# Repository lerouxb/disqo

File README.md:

# Disqo

A wearable synthesizer — a smartwatch with three buttons, a high-resolution magnetic scroll wheel and a circular LCD display, designed for building a synth you can run on your wrist.

## Hardware

Disqo is built around a custom PCB designed in KiCad.

| Component | Description |
|---|---|
| **ESP32-PICO-MINI-02** | Espressif SiP with 8 MB flash and 2 MB PSRAM |
| **GC9A01 round LCD** | 240×240 pixel 1.28" circular TFT display over SPI at 80 MHz |
| **AS5600** | 12-bit magnetic rotary encoder over I2C — acts as a high-resolution scroll wheel (like a watch crown) |
| **3 buttons** | Physical inputs for navigation, selection and sleep/wake |
| **Piezo buzzer** | PWM-driven audio output (beep/boop, future synth capabilities) |
| **MCP73831-2** | Single-cell Li-Po battery charger via USB |
| **32.768 kHz crystal** | External RTC clock source for accurate timekeeping |
| **Battery ADC** | Monitors battery voltage |

The PCB files, schematic, BOM and 3D models live in the `pcb/` directory. An interactive HTML BOM is available at `pcb/bom/ibom.html`.

## Firmware

The firmware runs on **MicroPython** with a patched [gc9a01_mpy](https://github.com/russhughes/gc9a01_mpy) C module compiled in for fast display drawing.

### Structure

```
firmware/
├── main.py              # Entry point — launches the watchface
├── boot.py              # MicroPython boot stub
├── apps/                # Applications (clock, main menu)
├── gui/                 # UI framework (menus, themes, text layout)
├── system/              # Hardware abstraction layer (HAL)
├── utils/               # Encoder math, datetime formatting, font helpers
├── fonts/               # Bitmap and TTF font definitions
├── scripts/             # Build, deploy and helper scripts
├── patches/             # Patches for gc9a01_mpy and MicroPython ESP32 port
└── typings/             # MicroPython type stubs for IDE support
```

### Watchface

The current primary watchface features:

- DSEG7-style digital clock with "ghost" segments
- Greeting text that changes by time of day (Good morning / afternoon / evening)
- Battery icon with voltage display
- Date with day-of-week
- Double-buffered rendering with a textured background

### Controls

- **Rotary encoder (scroll wheel):** Scrolls through menus and adjusts values
- **Button 1 (B1):** Wake from deep sleep; back/cancel in menus
- **Button 3 (B3):** Open main menu; select in menus
- **B1 + B3 combo:** Enter deep sleep

### Apps

- **Clock** — Date, time, battery status, encoder angle
- **Main Menu** — Scrollable menu with items: date/time, alarm, theme, brightness, metronome, drone (sub-apps are still planned)

## Building & Deploying

### Prerequisites

- MicroPython source
- ESP-IDF toolchain
- `esptool` and `mpremote`

### Compile MicroPython

The build script compiles MicroPython for the `GENERIC_SPIRAM` board with the patched `gc9a01_mpy` module:

```bash
cd firmware/scripts
./compile-micropython.sh
```

Patches are applied before building:

- **gc9a01_mpy.patch** — Faster display init, adds `draw_len` for text measurement
- **micropython-ports-esp32.patch** — Configures 80 MHz flash/SPIRAM, external RTC crystal, faster deep sleep wake

### Deploy code to device

```bash
cd firmware/scripts
./copy-code.sh
```

This uses `mpremote` to copy the Python source files to the device and syncs the RTC to the host clock.

### Set time

```bash
cd firmware/scripts
./set-time.sh
```

## Future Plans

- **Audio synthesis:** Wrap `pwm_audio` for better piezo output, classic Bluetooth audio, digital audio synthesis libraries
- **Sub-apps:** Date/time setting, alarm, theme selector, brightness control, metronome, drone
- Smarter input polling and debouncing
- Theme persistence in non-volatile memory

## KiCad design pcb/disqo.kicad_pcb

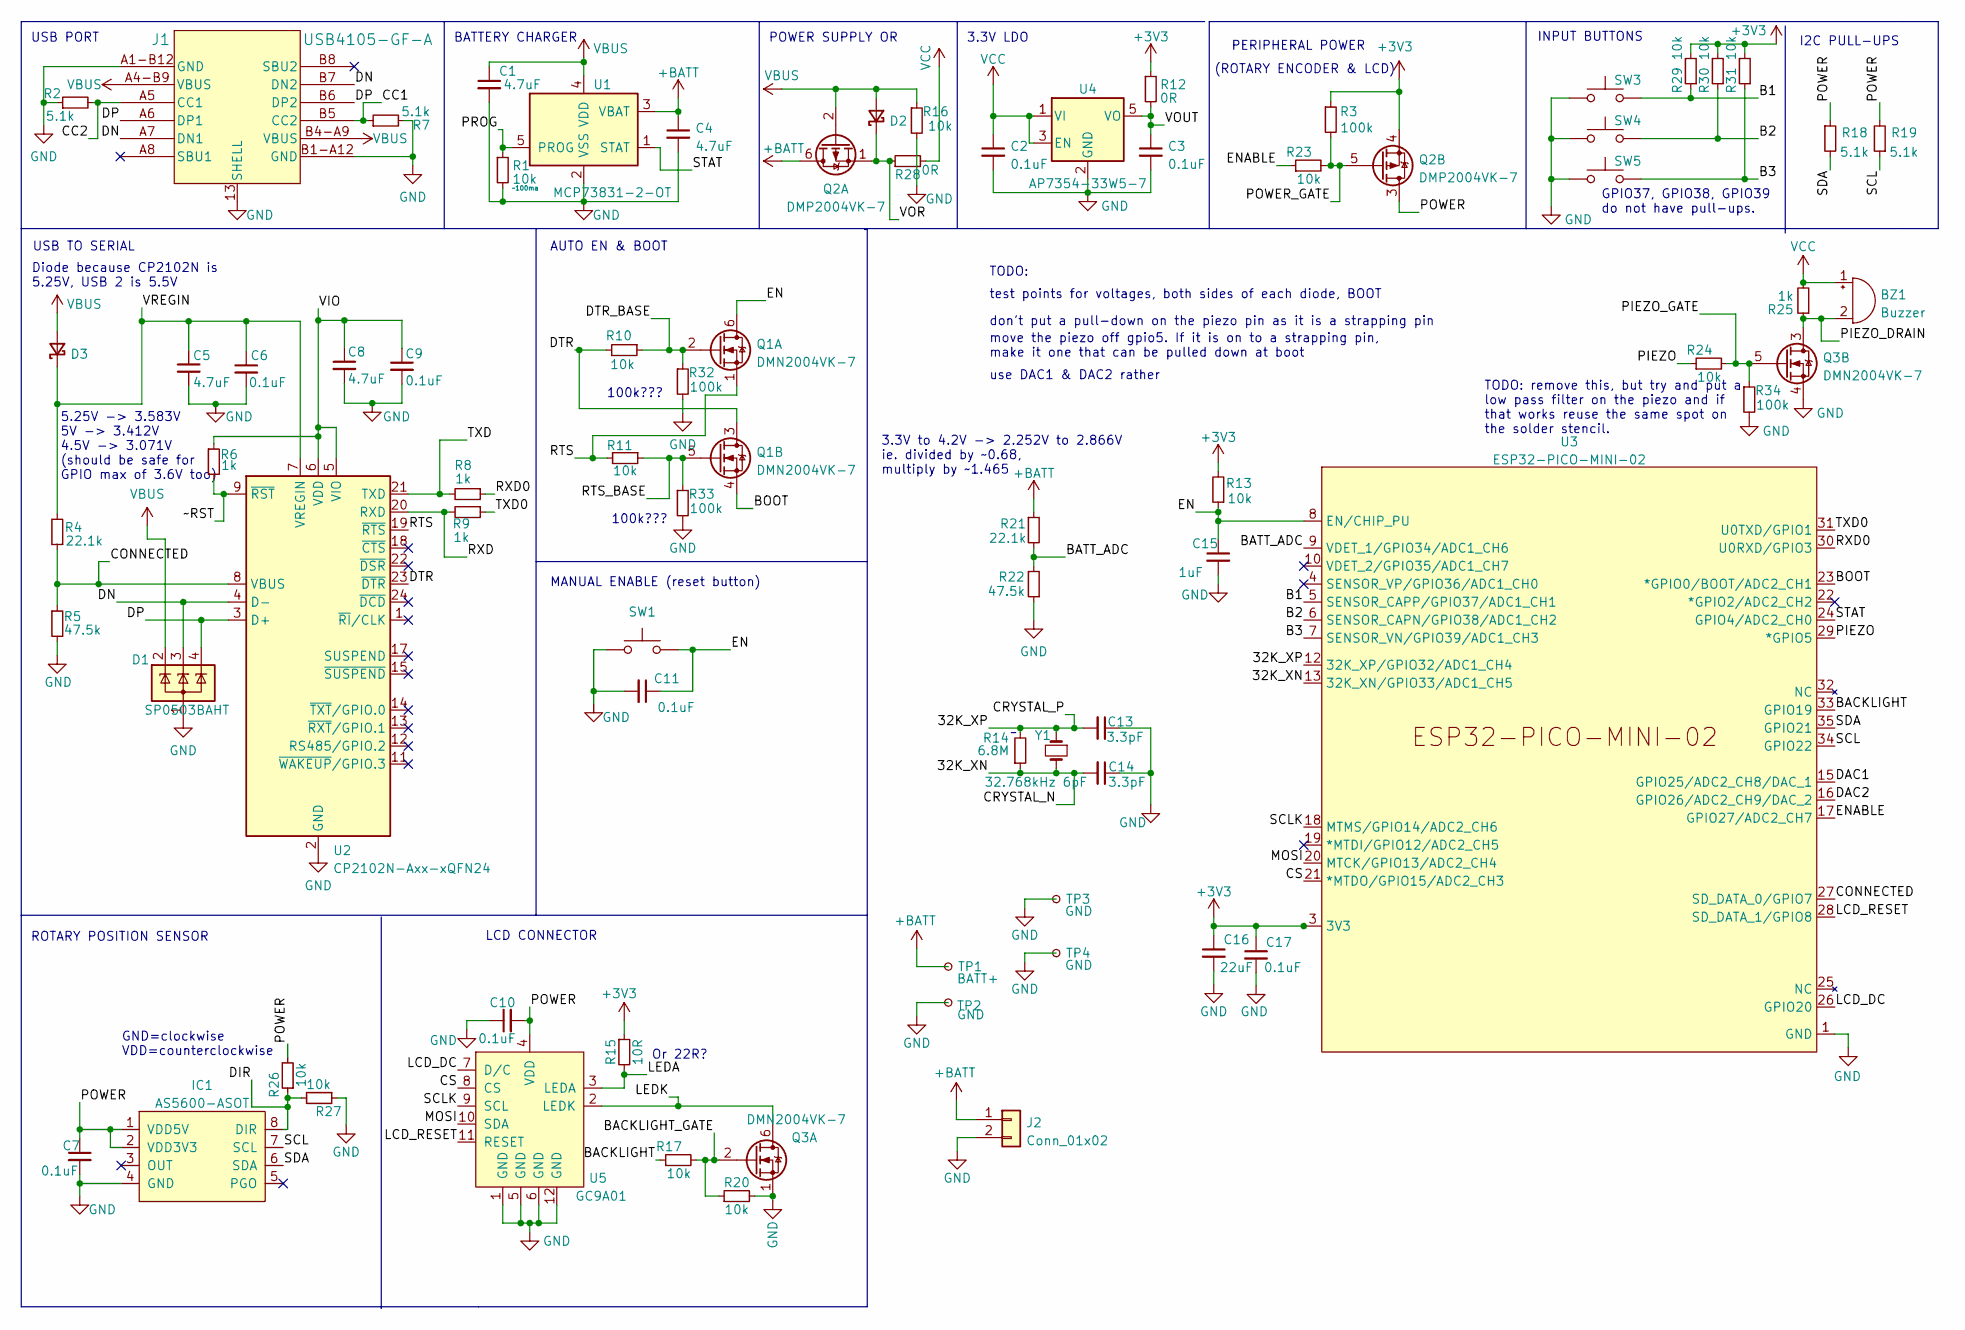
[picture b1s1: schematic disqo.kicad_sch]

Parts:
BZ1: Buzzer; SPKR_PKMCS0909E4000-R1
C1, C4, C5, C8: 4.7uF; C_0805_2012Metric
C2, C3, C6, C7, C9, C10, C11, C17: 0.1uF; C_0402_1005Metric
C13, C14: 3.3pF; C_0603_1608Metric
C15: 1uF; C_0603_1608Metric
C16: 22uF; C_0805_2012Metric
D1: SP0503BAHT; SOT-143
D2, D3: D_Schottky_Small; D_SOD-323
IC1: AS5600-ASOT; SOIC-8_3.9x4.9mm_P1.27mm; MOUSER_PART_NUMBER 985-AS5600-ASOT
J1: USB4105-GF-A
J2: Conn_01x02; JST_ACH_BM02B-ACHSS-GAN-ETF_1x02-1MP_P1.20mm_Vertical
Q1, Q3: DMN2004VK-7; SOT-563
Q2: DMP2004VK-7; SOT-563
R1, R10, R11, R13, R16, R17, R20, R23, R24, R26, R27, R29, R30, R31: 10k; R_0402_1005Metric
R2, R7, R18, R19: 5.1k; R_0402_1005Metric
R3, R32, R33, R34: 100k; R_0402_1005Metric
R4, R21: 22.1k; R_0402_1005Metric
R5, R22: 47.5k; R_0402_1005Metric
R6, R8, R9, R25: 1k; R_0402_1005Metric
R12, R28: 0R; R_0805_2012Metric
R14: 6.8M; R_0603_1608Metric
R15: 10R; R_0402_1005Metric
SW1: top-switch; KXT 311 LHS
SW3, SW4, SW5: side-switch; EVP-AKE31A
TP1: BATT+; TestPoint_THTPad_D1.5mm_Drill0.7mm
TP2: GND; TestPoint_THTPad_D1.5mm_Drill0.7mm
TP3, TP4: GND; tab
U1: MCP73831-2-OT; SOT-23-5
U2: CP2102N-Axx-xQFN24; QFN-24-1EP_4x4mm_P0.5mm_EP2.6x2.6mm
U3: ESP32-PICO-MINI-02; ESP32-PICO-MINI-02_Hand-Soldering
U4: AP7354-33W5-7; SOT-25
U5: GC9A01; GC9A01_IPS_display_under
Y1: 32.768kHz 6pF; Crystal_SMD_3215-2Pin_3.2x1.5mm

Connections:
+3V3: C16.1, C17.1, Q2.4 (S), R3.1, R12.1, R13.2, R15.1, R29.2, R30.2, R31.2, U3.3 (3V3)
+BATT: C4.1, J2.1, Q2.6 (D), R21.1, TP1.1, U1.3 (VBAT)
/32K_XN: C14.2, R14.1, U3.13 (32K_XN/GPIO33/ADC1_CH5), Y1.2
/32K_XP: C13.2, R14.2, U3.12 (32K_XP/GPIO32/ADC1_CH4), Y1.1
/B1: R29.1, SW3.1, U3.5 (SENSOR_CAPP/GPIO37/ADC1_CH1)
/B2: R30.1, SW4.1, U3.6 (SENSOR_CAPN/GPIO38/ADC1_CH2)
/B3: R31.1, SW5.2, U3.7 (SENSOR_VN/GPIO39/ADC1_CH3)
/BACKLIGHT: R17.1, U3.33 (GPIO19)
/BACKLIGHT_GATE: Q3.2 (G), R17.2, R20.1
/BATT_ADC: R21.2, R22.2, U3.9 (VDET_1/GPIO34/ADC1_CH6)
/BOOT: Q1.4 (S), U3.23 (*GPIO0/BOOT/ADC2_CH1)
/CC1: J1.B5 (CC2), R7.1
/CC2: J1.A5 (CC1), R2.2
/CONNECTED: R4.1, R5.1, U2.8 (VBUS), U3.27 (SD_DATA_0/GPIO7)
/CS: U3.21 (*MTDO/GPIO15/ADC2_CH3), U5.8 (CS)
/DAC1: U3.15 (GPIO25/ADC2_CH8/DAC_1)
/DAC2: U3.16 (GPIO26/ADC2_CH9/DAC_2)
/DIR: IC1.8 (DIR), R26.1, R27.2
/DN: D1.3 (K), J1.A7 (DN1), J1.B7 (DN2), U2.4 (D-)
/DP: D1.4 (K), J1.A6 (DP1), J1.B6 (DP2), U2.3 (D+)
/DTR: Q1.3 (D), R10.2, U2.23 (~DTR)
/DTR_BASE: Q1.2 (G), R10.1, R32.1
/EN: C11.1, C15.1, Q1.6 (D), R13.1, SW1.2, U3.8 (EN/CHIP_PU)
/ENABLE: R23.1, U3.17 (GPIO27/ADC2_CH7)
/LCD_DC: U3.26 (GPIO20), U5.7 (D/C)
/LCD_RESET: U3.28 (SD_DATA_1/GPIO8), U5.11 (RESET)
/LEDA: R15.2, U5.3 (LEDA)
/LEDK: Q3.6 (D), U5.2 (LEDK)
/MOSI: U3.20 (MTCK/GPIO13/ADC2_CH4), U5.10 (SDA)
/PIEZO: R24.1, U3.29 (*GPIO5)
/PIEZO_DRAIN: BZ1.2 (+), Q3.3 (D), R25.1
/PIEZO_GATE: Q3.5 (G), R24.2, R34.1
/POWER: C7.1, C10.2, IC1.1 (VDD5V), IC1.2 (VDD3V3), Q2.3 (D), R18.1, R19.2, R26.2, U5.4 (VDD)
/POWER_GATE: Q2.5 (G), R3.2, R23.2
/PROG: R1.1, U1.5 (PROG)
/RTS: Q1.1 (S), R11.2, U2.19 (~RTS)
/RTS_BASE: Q1.5 (G), R11.1, R33.1
/RXD: R9.2, U2.20 (RXD)
/RXD0: R8.1, U3.30 (U0RXD/GPIO3)
/SCL: IC1.7 (SCL), R19.1, U3.34 (GPIO22)
/SCLK: U3.18 (MTMS/GPIO14/ADC2_CH6), U5.9 (SCL)
/SDA: IC1.6 (SDA), R18.2, U3.35 (GPIO21)
/STAT: U1.1 (STAT), U3.24 (GPIO4/ADC2_CH0)
/TXD: R8.2, U2.21 (TXD)
/TXD0: R9.1, U3.31 (U0TXD/GPIO1)
/VIO: C8.1, C9.1, R6.1, U2.5 (VIO), U2.6 (VDD)
/VOR: D2.1 (K), Q2.1 (S), R28.1
/VOUT: C3.1, R12.2, U4.5 (VO)
/VREGIN: C5.1, C6.1, D3.1 (K), R4.2, U2.7 (VREGIN)
/~RST: R6.2, U2.9 (~RST)
GND: C1.2, C2.2, C3.2, C4.2, C5.2, C6.2, C7.2, C8.2, C9.2, C10.1, C11.2, C13.1, C14.1, C15.2, C16.2, C17.2, D1.1 (A), IC1.4 (GND), J1.13 (SHELL), J1.A1-B12 (GND), J1.B1-A12 (GND), J2.2, Q3.1 (S), Q3.4 (S), R1.2, R2.1, R5.2, R7.2, R16.2, R20.2, R22.1, R27.1, R32.2, R33.2, R34.2, SW1.1, SW3.2, SW4.2, SW5.1, TP2.1, TP3.1, TP4.1, U1.2 (VSS), U2.2 (GND), U2.25 (GND), U3.1 (GND), U3.2 (GND), U3.11 (GND), U3.14 (GND), U3.36 (GND), U4.2 (GND), U5.1 (GND), U5.5 (GND), U5.6 (GND), U5.12 (GND)
VBUS: C1.1, D1.2 (K), D2.2 (A), D3.2 (A), J1.A4-B9 (VBUS), J1.B4-A9 (VBUS), Q2.2 (G), R16.1, U1.4 (VDD)
VCC: BZ1.1 (-), C2.1, R25.2, R28.2, U4.1 (VI), U4.3 (EN)

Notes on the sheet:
POWER SUPPLY OR
use DAC1 & DAC2 rather
PERIPHERAL POWER
GPIO37, GPIO38, GPIO39 do not have pull-ups.
INPUT BUTTONS
3.3V LDO
(ROTARY ENCODER & LCD)
move the piezo off gpio5. If it is on to a strapping pin, make it one that can be pulled down at boot
5.25V -> 3.583V 5V -> 3.412V 4.5V -> 3.071V (should be safe for GPIO max of 3.6V too)
I2C PULL-UPS
100k???
USB TO SERIAL
TODO: remove this, but try and put a low pass filter on the piezo and if that works reuse the same spot on the solder stencil.
LCD CONNECTOR
AUTO EN & BOOT
Or 22R?
BATTERY CHARGER
don't put a pull-down on the piezo pin as it is a strapping pin
USB PORT
GND=clockwise VDD=counterclockwise
MANUAL ENABLE (reset button)
3.3V to 4.2V -> 2.252V to 2.866V ie. divided by ~0.68, multiply by ~1.465
test points for voltages, both sides of each diode, BOOT
Diode because CP2102N is 5.25V, USB 2 is 5.5V
ROTARY POSITION SENSOR
TODO:

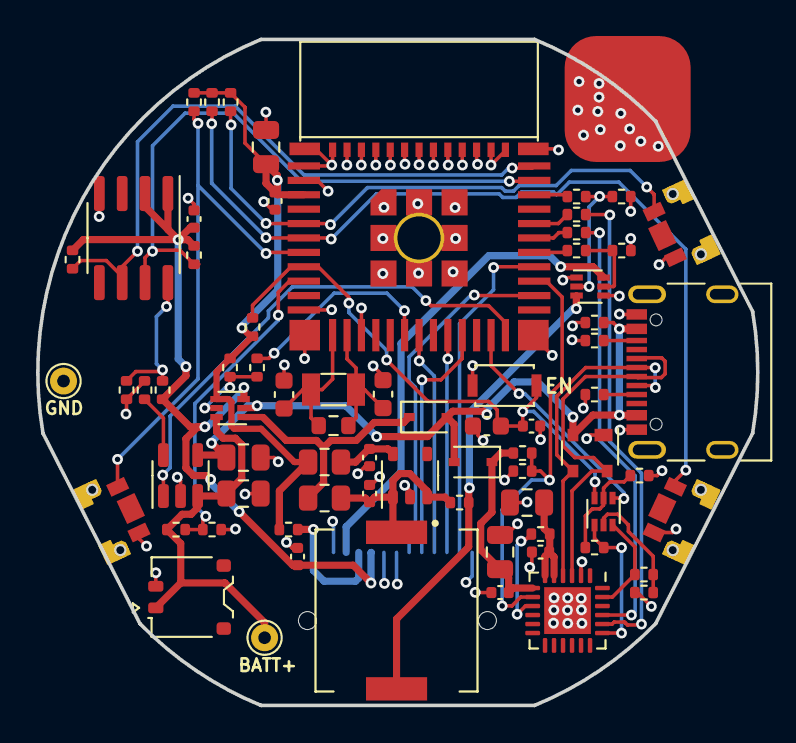
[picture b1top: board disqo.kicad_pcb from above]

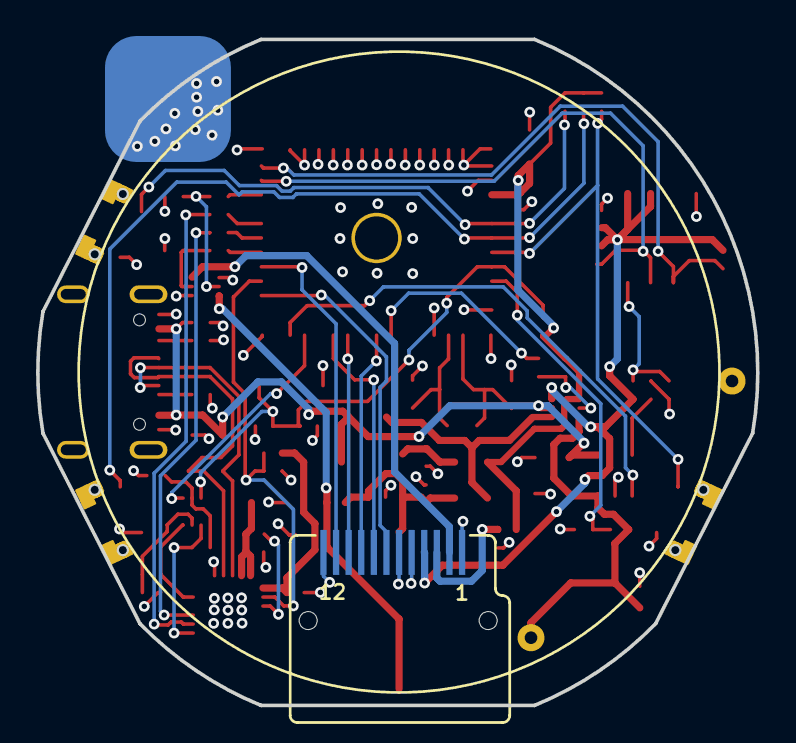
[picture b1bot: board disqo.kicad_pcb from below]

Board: 4 copper layers, 40.0 x 37.0 mm, 74 parts (2 on the bottom side), 51 nets.

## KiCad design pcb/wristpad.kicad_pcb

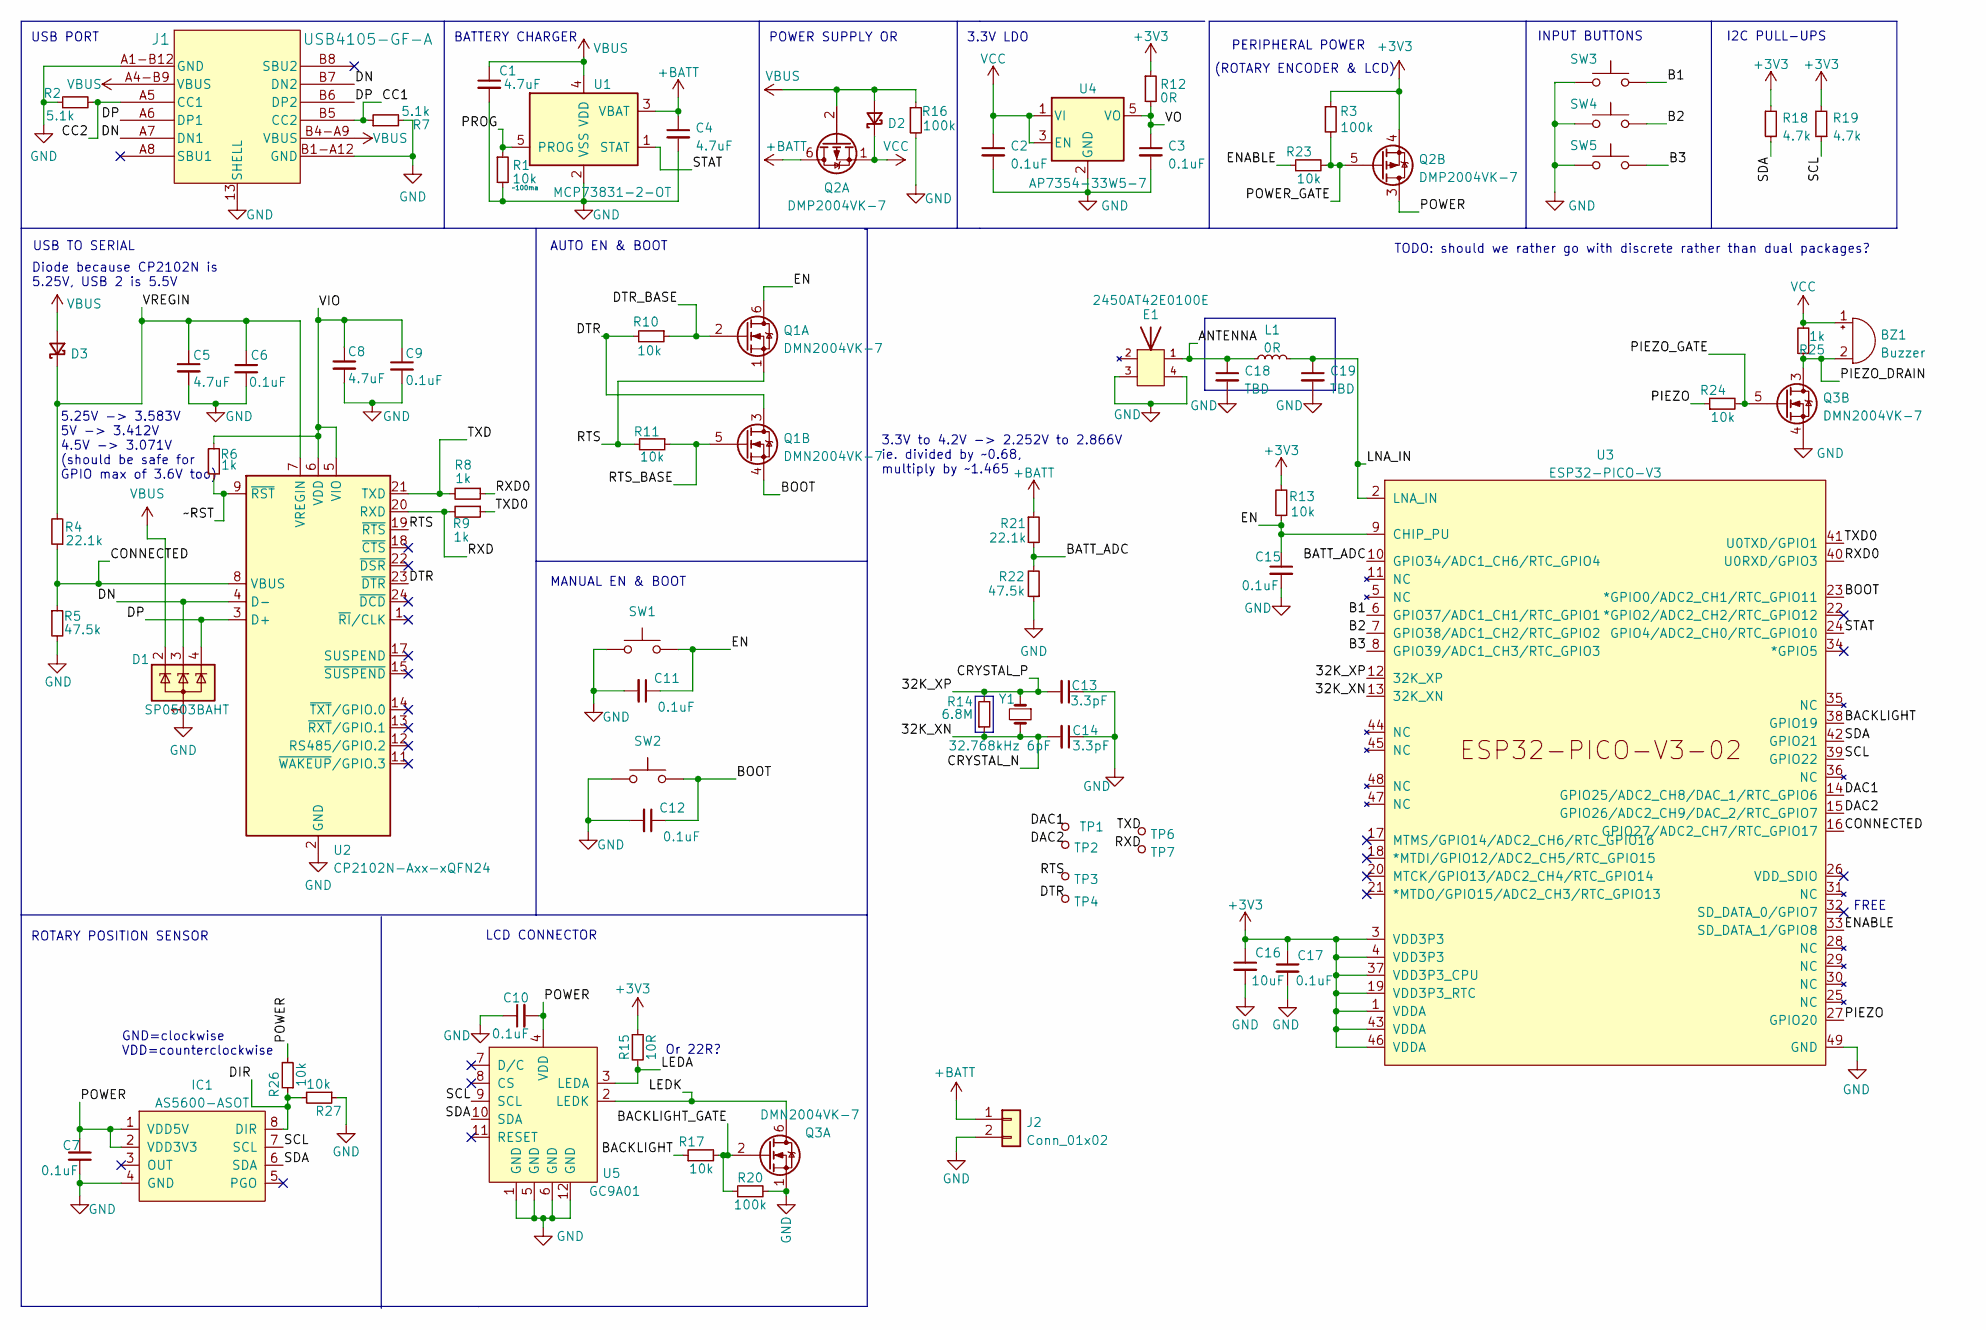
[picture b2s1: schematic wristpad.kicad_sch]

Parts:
BZ1: Buzzer; SPKR_PKMCS0909E4000-R1
C1, C4, C5, C8: 4.7uF; C_0402_1005Metric
C2, C3, C6, C7, C9, C10, C11, C12, C15, C17: 0.1uF; C_0402_1005Metric
C13, C14: 3.3pF; C_0603_1608Metric
C16: 10uF; C_0402_1005Metric
C18, C19: TBD; C_0603_1608Metric
D1: SP0503BAHT; SOT-143
D2, D3: D_Schottky_Small; D_SOD-323
E1: 2450AT42E0100E; XDCR_2450AT42E0100E; PARTREV 1.3
IC1: AS5600-ASOT; SOIC-8_3.9x4.9mm_P1.27mm; MOUSER_PART_NUMBER 985-AS5600-ASOT
J1: USB4105-GF-A
J2: Conn_01x02; Battery Connector
L1: 0R; L_0603_1608Metric
Q1, Q3: DMN2004VK-7; SOT-563
Q2: DMP2004VK-7; SOT-563
R1, R10, R11, R13, R17, R23, R24, R26, R27: 10k; R_0402_1005Metric
R2, R7: 5.1k; R_0402_1005Metric
R3, R16, R20: 100k; R_0402_1005Metric
R4, R21: 22.1k; R_0402_1005Metric
R5, R22: 47.5k; R_0402_1005Metric
R6, R8, R9, R25: 1k; R_0402_1005Metric
R12: 0R; R_0805_2012Metric
R14: 6.8M
R15: 10R; R_0402_1005Metric
R18, R19: 4.7k; R_0402_1005Metric
SW1, SW2: top-switch; KXT 311 LHS
SW3, SW4, SW5: side-switch; EVP-AKE31A
TP1: DAC1; TestPoint_Pad_D1.0mm
TP2: DAC2; TestPoint_Pad_D1.0mm
TP3: RTS; TestPoint_Pad_D1.0mm
TP4: DTR; TestPoint_Pad_D1.0mm
TP6: TXD; TestPoint_Pad_D1.0mm
TP7: RXD; TestPoint_Pad_D1.0mm
U1: MCP73831-2-OT; SOT-23-5
U2: CP2102N-Axx-xQFN24; QFN-24-1EP_4x4mm_P0.5mm_EP2.6x2.6mm
U3: ESP32-PICO-V3; QFN-48-1EP_7x7mm_P0.5mm_EP5.15x5.15mm
U4: AP7354-33W5-7; SOT-25
U5: GC9A01; GC9A01_IPS_display_under
Y1: 32.768kHz 6pF; Crystal_SMD_3215-2Pin_3.2x1.5mm

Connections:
+3V3: C16.1, C17.1, Q2.4 (S), R3.1, R12.1, R13.2, R15.1, R18.1, R19.2, U3.1 (VDDA), U3.3 (VDD3P3), U3.4 (VDD3P3), U3.19 (VDD3P3_RTC), U3.37 (VDD3P3_CPU), U3.43 (VDDA), U3.46 (VDDA)
+BATT: C4.1, J2.1, Q2.6 (D), R21.1, U1.3 (VBAT)
/32K_XN: C14.2, R14.1, U3.13 (32K_XN), Y1.2
/32K_XP: C13.2, R14.2, U3.12 (32K_XP), Y1.1
/ANTENNA: C18.1, E1.1, L1.1
/B1: SW3.2, U3.6 (GPIO37/ADC1_CH1/RTC_GPIO1)
/B2: SW4.2, U3.7 (GPIO38/ADC1_CH2/RTC_GPIO2)
/B3: SW5.2, U3.8 (GPIO39/ADC1_CH3/RTC_GPIO3)
/BACKLIGHT: R17.1, U3.38 (GPIO19)
/BACKLIGHT_GATE: Q3.2 (G), R17.2, R20.1
/BATT_ADC: R21.2, R22.2, U3.10 (GPIO34/ADC1_CH6/RTC_GPIO4)
/BOOT: C12.1, Q1.4 (S), SW2.2, U3.23 (*GPIO0/ADC2_CH1/RTC_GPIO11)
/CC1: J1.B5 (CC2), R7.1
/CC2: J1.A5 (CC1), R2.2
/CONNECTED: R4.1, R5.1, U2.8 (VBUS), U3.16 (GPIO27/ADC2_CH7/RTC_GPIO17)
/DAC1: TP1.1, U3.14 (GPIO25/ADC2_CH8/DAC_1/RTC_GPIO6)
/DAC2: TP2.1, U3.15 (GPIO26/ADC2_CH9/DAC_2/RTC_GPIO7)
/DIR: IC1.8 (DIR), R26.1, R27.2
/DN: D1.3 (K), J1.A7 (DN1), J1.B7 (DN2), U2.4 (D-)
/DP: D1.4 (K), J1.A6 (DP1), J1.B6 (DP2), U2.3 (D+)
/DTR: Q1.3 (D), R10.2, TP4.1, U2.23 (~DTR)
/DTR_BASE: Q1.2 (G), R10.1
/EN: C11.1, C15.1, Q1.6 (D), R13.1, SW1.2, U3.9 (CHIP_PU)
/ENABLE: R23.1, U3.33 (SD_DATA_1/GPIO8)
/LEDA: R15.2, U5.3 (LEDA)
/LEDK: Q3.6 (D), U5.2 (LEDK)
/LNA_IN: C19.1, L1.2, U3.2 (LNA_IN)
/PIEZO: R24.1, U3.27 (GPIO20)
/PIEZO_DRAIN: BZ1.2 (+), Q3.3 (D), R25.1
/PIEZO_GATE: Q3.5 (G), R24.2
/POWER: C7.1, C10.2, IC1.1 (VDD5V), IC1.2 (VDD3V3), Q2.3 (D), R26.2, U5.4 (VDD)
/POWER_GATE: Q2.5 (G), R3.2, R23.2
/PROG: R1.1, U1.5 (PROG)
/RTS: Q1.1 (S), R11.2, TP3.1, U2.19 (~RTS)
/RTS_BASE: Q1.5 (G), R11.1
/RXD: R9.2, TP7.1, U2.20 (RXD)
/RXD0: R8.1, U3.40 (U0RXD/GPIO3)
/SCL: IC1.7 (SCL), R19.1, U3.39 (GPIO22), U5.9 (SCL)
/SDA: IC1.6 (SDA), R18.2, U3.42 (GPIO21), U5.10 (SDA)
/STAT: U1.1 (STAT), U3.24 (GPIO4/ADC2_CH0/RTC_GPIO10)
/TXD: R8.2, TP6.1, U2.21 (TXD)
/TXD0: R9.1, U3.41 (U0TXD/GPIO1)
/VIO: C8.1, C9.1, R6.1, U2.5 (VIO), U2.6 (VDD)
/VO: C3.1, R12.2, U4.5 (VO)
/VREGIN: C5.1, C6.1, D3.1 (K), R4.2, U2.7 (VREGIN)
/~RST: R6.2, U2.9 (~RST)
GND: C1.2, C2.2, C3.2, C4.2, C5.2, C6.2, C7.2, C8.2, C9.2, C10.1, C11.2, C12.2, C13.1, C14.1, C15.2, C16.2, C17.2, C18.2, C19.2, D1.1 (A), E1.3, E1.4, IC1.4 (GND), J1.13 (SHELL), J1.A1-B12 (GND), J1.B1-A12 (GND), J2.2, Q3.1 (S), Q3.4 (S), R1.2, R2.1, R5.2, R7.2, R16.2, R20.2, R22.1, R27.1, SW1.1, SW2.1, SW3.1, SW4.1, SW5.1, U1.2 (VSS), U2.2 (GND), U2.25 (GND), U3.49 (GND), U4.2 (GND), U5.1 (GND), U5.5 (GND), U5.6 (GND), U5.12 (GND)
VBUS: C1.1, D1.2 (K), D2.2 (A), D3.2 (A), J1.A4-B9 (VBUS), J1.B4-A9 (VBUS), Q2.2 (G), R16.1, U1.4 (VDD)
VCC: BZ1.1 (-), C2.1, D2.1 (K), Q2.1 (S), R25.2, U4.1 (VI), U4.3 (EN)

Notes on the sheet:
POWER SUPPLY OR
PERIPHERAL POWER
INPUT BUTTONS
3.3V LDO
(ROTARY ENCODER & LCD)
5.25V -> 3.583V 5V -> 3.412V 4.5V -> 3.071V (should be safe for GPIO max of 3.6V too)
I2C PULL-UPS
USB TO SERIAL
LCD CONNECTOR
AUTO EN & BOOT
Or 22R?
BATTERY CHARGER
USB PORT
GND=clockwise VDD=counterclockwise
MANUAL EN & BOOT
FREE
3.3V to 4.2V -> 2.252V to 2.866V ie. divided by ~0.68, multiply by ~1.465
TODO: should we rather go with discrete rather than dual packages?
Diode because CP2102N is 5.25V, USB 2 is 5.5V
ROTARY POSITION SENSOR

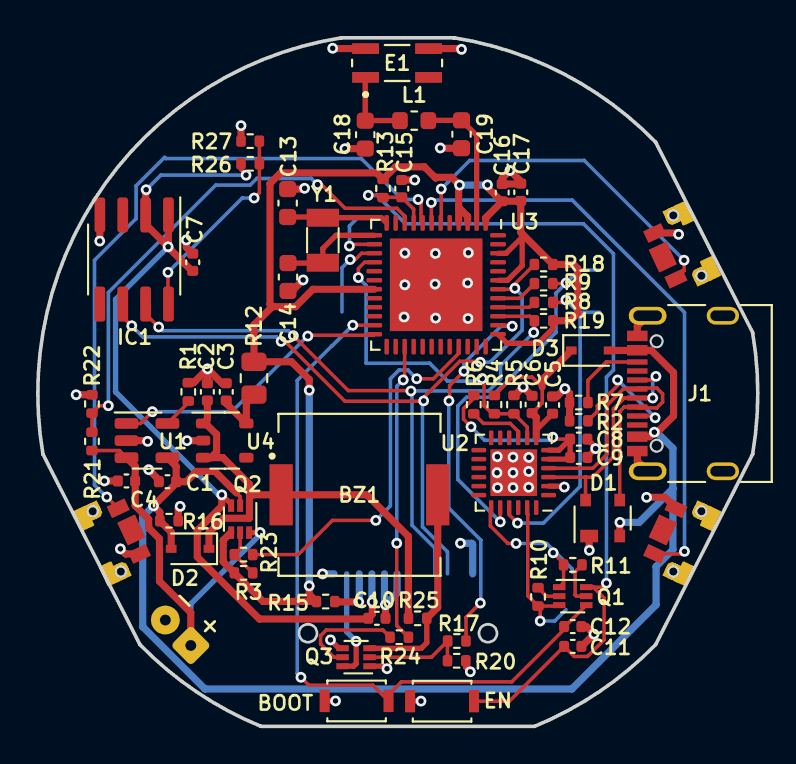
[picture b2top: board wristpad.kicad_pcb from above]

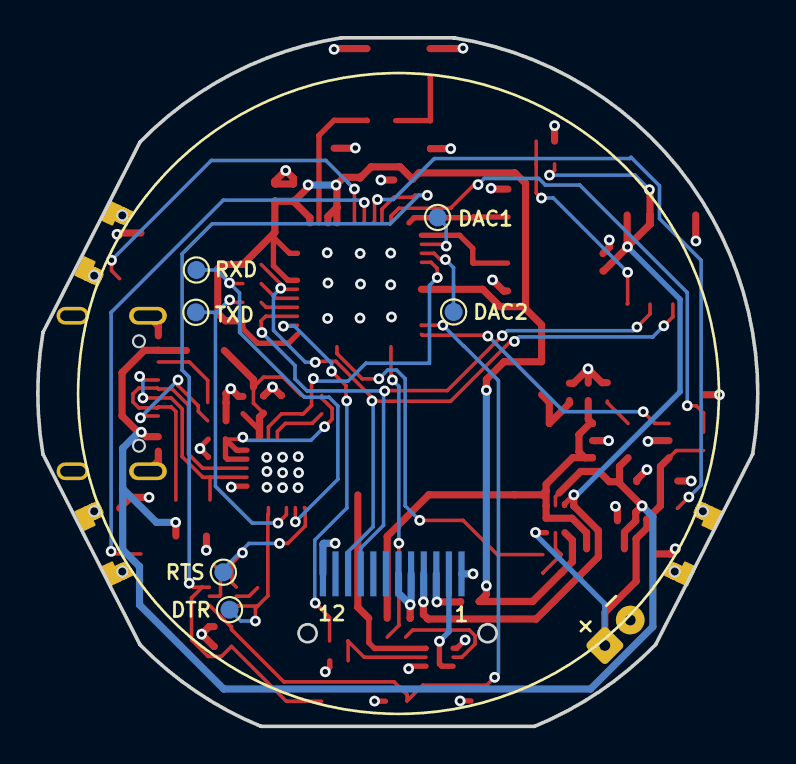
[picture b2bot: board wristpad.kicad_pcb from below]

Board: 4 copper layers, 40.0 x 38.3 mm, 74 parts (7 on the bottom side), 49 nets.

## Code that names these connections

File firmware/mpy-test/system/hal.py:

import time
import machine
from machine import SPI, I2C, ADC, Pin, PWM, RTC
import gc9a01
import esp32

LAST_TIME = time.ticks_ms()

def bench(name):
    global LAST_TIME
    new_time = time.ticks_ms()
    print(name, new_time - LAST_TIME)
    LAST_TIME = new_time


ENCODER_ADDRESS = 54

class AttrDict(dict):
    def __getattr__(self, name):
        return self[name]

PINS = AttrDict(
    SCK=14,
    MOSI=13,
    SCL=22,
    SDA=21,
    B1=37,
    B2=38,
    B3=39,
    POWER_DISABLE=27,
    USB_CONNECTED=7,
    BATTERY_CHARGING=4,
    BATTERY_ADC=34,
    LCD_RESET=8,
    LCD_DC=20,
    LCD_CS=15,
    LCD_BACKLIGHT=19,
    PIEZO=5
)

piezo = Pin(PINS.PIEZO, Pin.OUT)
piezo.value(False) # a known value
piezo_pwm = PWM(piezo)

i2c = I2C(0, scl=Pin(PINS.SCL), sda=Pin(PINS.SDA), freq=400000)

buttons = AttrDict(
    b1=Pin(PINS.B1, Pin.IN),
    b2=Pin(PINS.B2, Pin.IN),
    b3=Pin(PINS.B3, Pin.IN)
)

power_disable = Pin(PINS.POWER_DISABLE, Pin.OUT)
power_disable.value(False) # enable power

usb_connected = Pin(PINS.USB_CONNECTED, Pin.IN)

# necessity of PULL kinda depends on how to deal with various High-Z states
# and whether it is MCP73831 or MCP73832
# MCP73831 is Charge Complete – Standby HIGH
# MCP73832 is Charge Complete – Standby HIGH-Z
# Both are Preconditioning, Constant-Current Fast Charge and Constant Voltage LOW
# Both are Shutdown and No Battery Present HIGH-Z
battery_charging = Pin(PINS.BATTERY_CHARGING, Pin.IN, Pin.PULL_UP) 
battery_adc = ADC(Pin(PINS.BATTERY_ADC, Pin.IN), atten=ADC.ATTN_11DB)
# battery_adc.read_uv() / 1000000 * 1.465

esp32.wake_on_ext0(buttons.b1, esp32.WAKEUP_ALL_LOW)

rtc = RTC()

DISPLAY_WIDTH = 240
HALF_DISPLAY_WIDTH = 120
DISPLAY_HEIGHT = 240
HALF_DISPLAY_HEIGHT = 120

def beep():
    piezo_pwm.duty_u16(880)
    piezo_pwm.freq(880)
    time.sleep(0.1)
    piezo_pwm.duty_u16(0)

def boop():
    piezo_pwm.duty_u16(261)
    piezo_pwm.freq(261)
    time.sleep(0.1)
    piezo_pwm.duty_u16(0)

beep()

spi = SPI(1, baudrate=60000000, sck=Pin(PINS.SCK), mosi=Pin(PINS.MOSI))
# no idea what buffer size we need
lcd = gc9a01.GC9A01(spi, width=240, height=240, buffer_size=1024, dc=Pin(PINS.LCD_DC, Pin.OUT), cs=Pin(PINS.LCD_CS, Pin.OUT), reset=Pin(PINS.LCD_RESET, Pin.OUT))
lcd.init()
lcd.fill(0)

lcd_backlight = Pin(PINS.LCD_BACKLIGHT)
lcd_pwm = PWM(lcd_backlight)
lcd_pwm.duty(128) # 0 to 1023

def read_angle():
    while True:
        try:
            return int.from_bytes(i2c.readfrom_mem(ENCODER_ADDRESS, 0x0E, 2), 'big')
        except OSError:
            print("error")
            pass

def deepsleep():
    machine.deepsleep()

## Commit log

2022-10-27 panelized, fixes
2022-11-14 rename
2022-12-24 PCB tweaks
2022-12-24 readme
2022-12-25 basic firmware
2022-12-30 add gc9a01
2022-12-31 another font
2023-01-21 pcb changes
2023-03-04 firmware tweaks
2023-03-04 ignore
2023-03-04 c firmware test changes
2023-03-07 beginnings of a launcher
2023-04-25 incorporate ttf fonts
2023-04-27 start of a new face
2023-05-09 tweaks
2023-05-09 larger icon font
2023-05-09 bring back the ghost
2023-06-19 flatten
2026-03-28 add a readme
